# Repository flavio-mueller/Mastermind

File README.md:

# Mastermind
This is a Project guided by the FHNW for SJF.

Useful links:

[ampy-tool](https://github.com/adafruit/ampy): used to deploy your files.

[MobaXterm](http://mobaxterm.mobatek.net/): Used to watch the COM-Serial-Connection.

[3D-Model of the Case](http://a360.co/2vZlHcu):

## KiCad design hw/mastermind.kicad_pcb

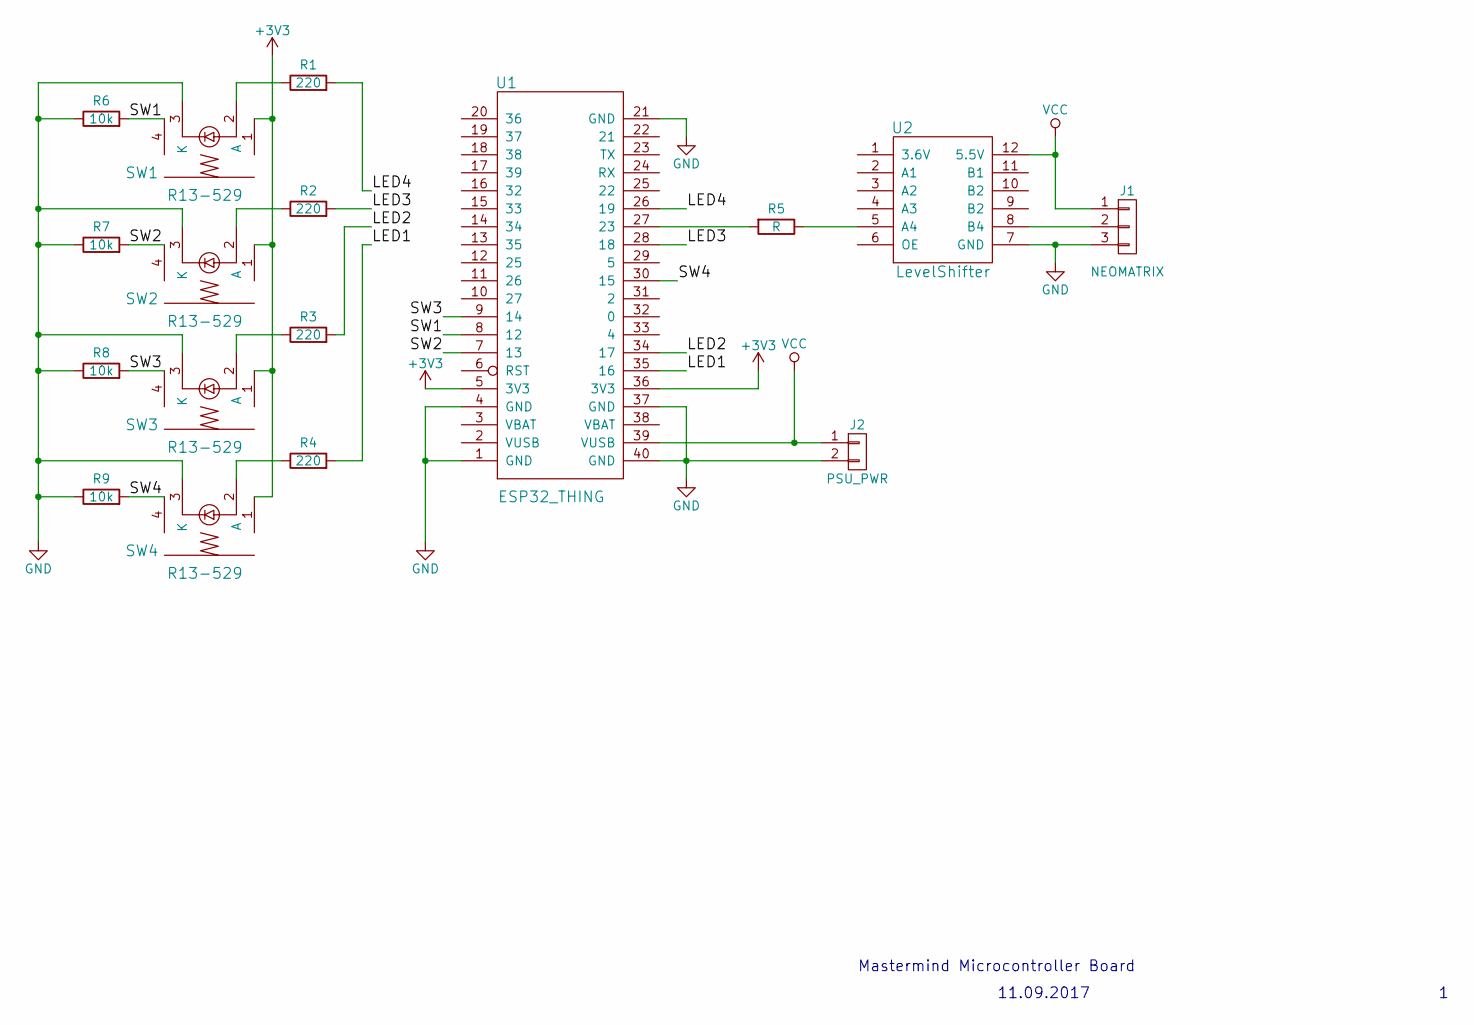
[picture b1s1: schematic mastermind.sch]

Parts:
J1: NEOMATRIX; Pin_Header_Straight_1x03_Pitch2.00mm
J2: PSU_PWR; Pin_Header_Straight_1x02_Pitch2.00mm
R1, R2, R3, R4: 220; R_Axial_DIN0207_L6.3mm_D2.5mm_P10.16mm_Horizontal
R5: R; R_Axial_DIN0207_L6.3mm_D2.5mm_P10.16mm_Horizontal
R6, R7, R8, R9: 10k; R_Axial_DIN0207_L6.3mm_D2.5mm_P10.16mm_Horizontal
SW1, SW2, SW3, SW4: R13-529; Pin_Header_Straight_1x04_Pitch2.54mm
U1: ESP32_THING
U2: LevelShifter

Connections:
+3V3: SW1.1, SW2.1, SW3.1, SW4.1, U1.5 (3V3), U1.36 (3V3)
/LED1: R4.2, U1.35 (16)
/LED2: R3.2, U1.34 (17)
/LED3: R2.2, U1.28 (18)
/LED4: R1.2, U1.26 (19)
/SW1: R6.2, SW1.4, U1.8 (12)
/SW2: R7.2, SW2.4, U1.7 (13)
/SW3: R8.2, SW3.4, U1.9 (14)
/SW4: R9.2, SW4.4, U1.30 (15)
GND: J1.3, J2.2, R6.1, R7.1, R8.1, R9.1, SW1.3 (K), SW2.3 (K), SW3.3 (K), SW4.3 (K), U1.1 (GND), U1.4 (GND), U1.21 (GND), U1.37 (GND), U1.40 (GND), U2.7 (GND)
unnamed: J1.2, U2.8 (B4)
unnamed: R1.1, SW1.2 (A)
unnamed: R2.1, SW2.2 (A)
unnamed: R3.1, SW3.2 (A)
unnamed: R4.1, SW4.2 (A)
unnamed: R5.1, U2.5 (A4)
unnamed: R5.2, U1.27 (23)
VCC: J1.1, J2.1, U1.39 (VUSB), U2.12 (5.5V)

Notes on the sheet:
11.09.2017
Mastermind Microcontroller Board

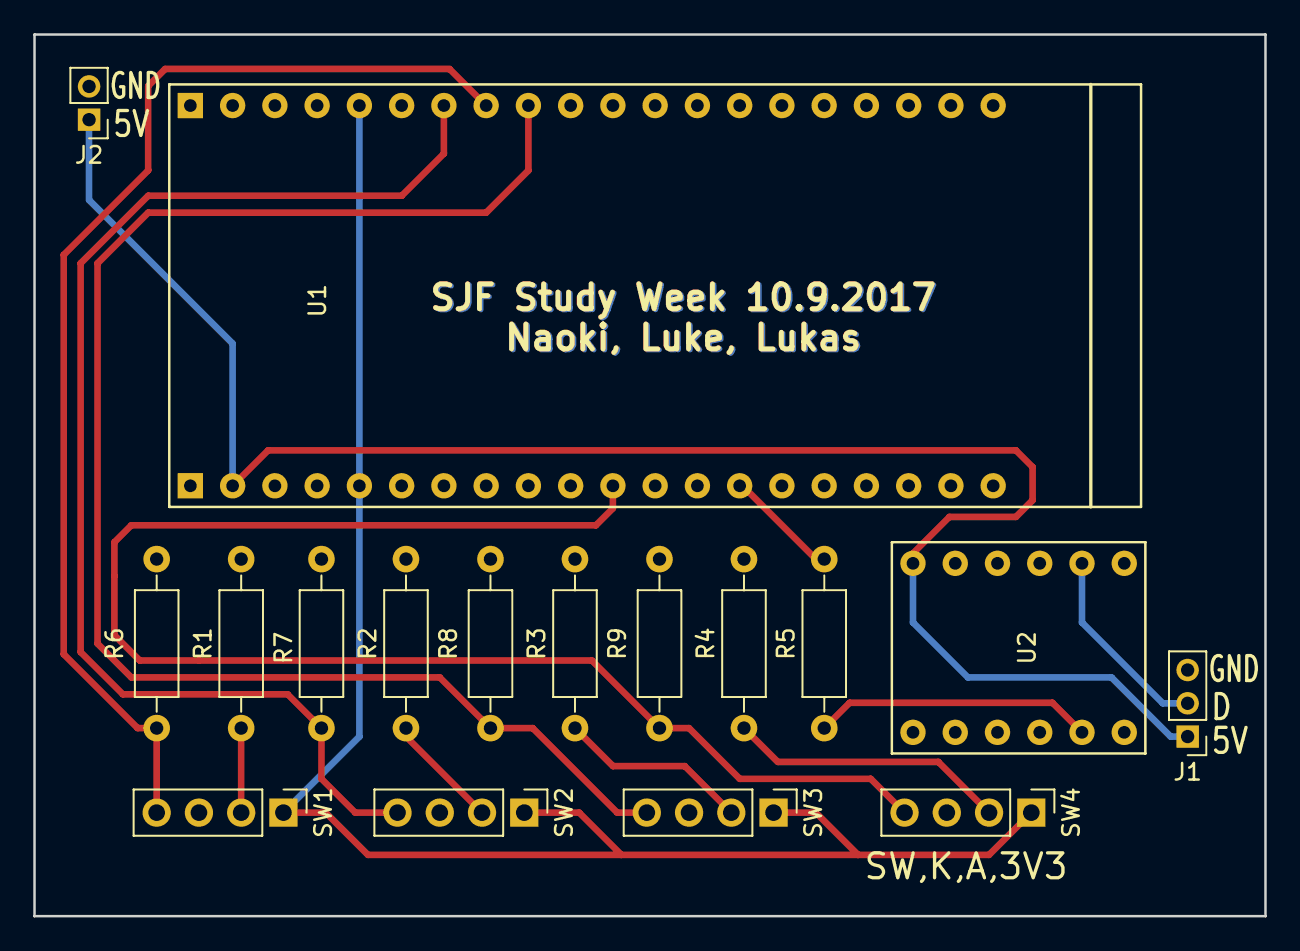
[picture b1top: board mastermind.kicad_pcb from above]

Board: 2 copper layers, 74.0 x 53.0 mm, 17 parts (0 on the bottom side), 18 nets.

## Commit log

2017-09-11 Add current work to Git
    Description of the content:
    datasheets/ Datasheets for various components used in the project
    doc/ Documentation (empty)
    hw/ KiCad documents for hardware design (PCB)
    notes/ Miscellaneous documents about the project
    src/ Python source code for MicroPython
2017-09-11 basic implementation for the main code flow
    Game flags are still missing (hints by the codemaker)
2017-09-12 Initial post
    main.py: algorithm which solves the game
2017-09-12 9/11 couln't have been an inside job because the planes came from the outside
    Moved to Github :)
2017-09-12 fixed typo
2017-09-12 redesign of the entire pcb to match physical dimensions requirements
2017-09-12 microcotroler program added
    first version of the microcontroler programm it let's the user input a
    colorcode for the algorithm
2017-09-12 add ceck state. Not sure if works
2017-09-12 pls not screw pls
2017-09-12 Fixed the microcontroler script
    Algorithm now plays the game and displays it on the matrix.
    No ram problems anymore
2017-09-12 Add power input header and a few corrections
2017-09-12 Working player Mode
2017-09-12 Desktop version of mastermind and nonworking micro version prototype
    Probably I won't update this code (unless I got time to spare), since
    Lukas's code is working.
2017-09-13 Created a jump'n run
    Created a jump'n run that should work on the microcontroler
2017-09-13 Now displays gamestate on matrix
2017-09-13 Added some flashy lights :P
2017-09-13 added autosolve to game
    Added autosolve algorithm to lukas mastermind implementation in
    mastermind2.0.py
2017-09-13 bugfix
2017-09-13 added AutoGuess and AutoSet
2017-09-14 add hw test unit code
2017-09-14 Addd Autosolve thingy, not enough ram
2017-09-14 Small fix
2017-09-14 Redoing PCB design because there are a few mistakes
2017-09-14 Finished game but auto solve not working yet
2017-09-14 Clean up solver code in a new file `solver.py'
2017-09-14 Cleanup in the src directory
2017-09-14 Added delay in the algorithm loop
2017-09-14 Added delay to the algorithm loop
2017-09-25 Moved Luke's work into its own directory
2017-10-06 Documentation with LaTeX!
    The documentation has now been moved to LaTeX, since google docs had
    many problems with figures and captions.
2017-10-06 Update gitignore to include a compiled document
2017-10-08 Doc corrections and styling fix, new file `mastermind_nf' that uses the default latex settings (mostly).
2017-10-08 Layout fix
